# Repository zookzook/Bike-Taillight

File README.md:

# Bike-Taillight
Schema for led driven bike taillight

Combining two simple standard circuits, you get a solid circuit for a bicycle rear light, which 
is operated by an LED. The circuit is simple. You need a constant current source for the LED 
and a Delon circuit as a bridge circuit.

The Delon circuit provides a DC voltage, where the voltage is doubled. This will provide up to 14 volts.
At the output of the Delon circuit is the constant current source with an NPN transsistor. Two 1N4148 diodes are used for biasing and will give approximately 1.4 volts. The current is determined via R2 and is calculated as (1.4 - 0.7) / R2. The circuit would use 47 ohms for R2 and therefore a current of approximately 15 mA should flow.

Depending on the transistor, the value may change slightly and depending on the LED used, the value can be adjusted via R2. 

Both circuits are described in every good electronics manual, so there is no magic at all!

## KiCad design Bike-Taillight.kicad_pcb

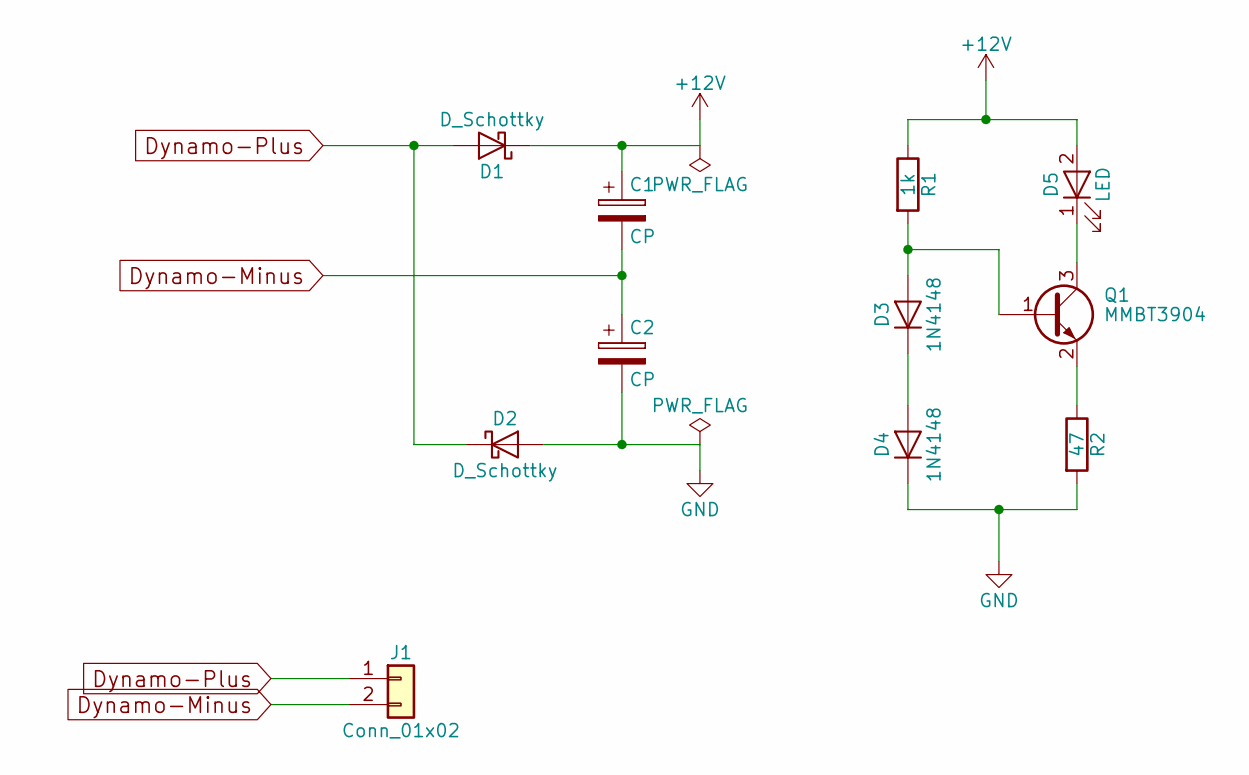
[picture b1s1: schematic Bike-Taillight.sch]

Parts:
C1, C2: CP; CP_Elec_5x5.8
D1, D2: D_Schottky; D_2114
D3, D4: 1N4148; D_SOD-123
D5: LED; LED-5MM
J1: Conn_01x02; Pin_Header_Angled_1x02
Q1: MMBT3904; SOT-23_Handsoldering
R1: 1k; R_0805_HandSoldering
R2: 47; R_0805_HandSoldering

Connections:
+12V: C1.1, D1.1 (K), D5.2 (A), R1.1
Dynamo-Minus: C1.2, C2.1, J1.2
Dynamo-Plus: D1.2 (A), D2.1 (K), J1.1
GND: C2.2, D2.2 (A), D4.1 (K), R2.2
unnamed: D3.1 (K), D4.2 (A)
unnamed: D3.2 (A), Q1.1 (B), R1.2
unnamed: D5.1 (K), Q1.3 (C)
unnamed: Q1.2 (E), R2.1

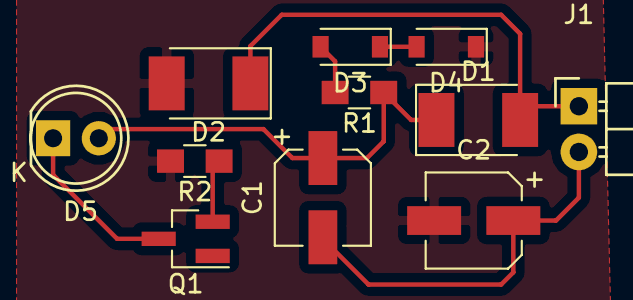
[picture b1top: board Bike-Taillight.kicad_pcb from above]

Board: 2 copper layers, 11 parts (0 on the bottom side), 8 nets.

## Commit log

2017-12-25 Update .gitignore
    KiCad ignore template
2017-12-25 First version
2017-12-25 Schema.png added
